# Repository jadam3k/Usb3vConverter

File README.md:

# USB Mini to 3.3V Converter

A simple USB mini to 3.3V converter: easy to build, reliable, and perfect for small electronics projects.

| Interested? [Follow the project!](https://blueprint.hackclub.com/projects/2747?return_to=%2Fusers%2F2170)|
|------------------------------------|

This project focuses on simplicity while providing stable 3.3V output from a USB mini connector.  

## Features

- USB Mini input
- 3.3V regulated output
- Compact PCB design
- Only 3 integrated circuits needed
- Easy to solder and assemble
- Suitable for powering small electronics or logic circuits  

The PCB layout is designed to be simple ;)

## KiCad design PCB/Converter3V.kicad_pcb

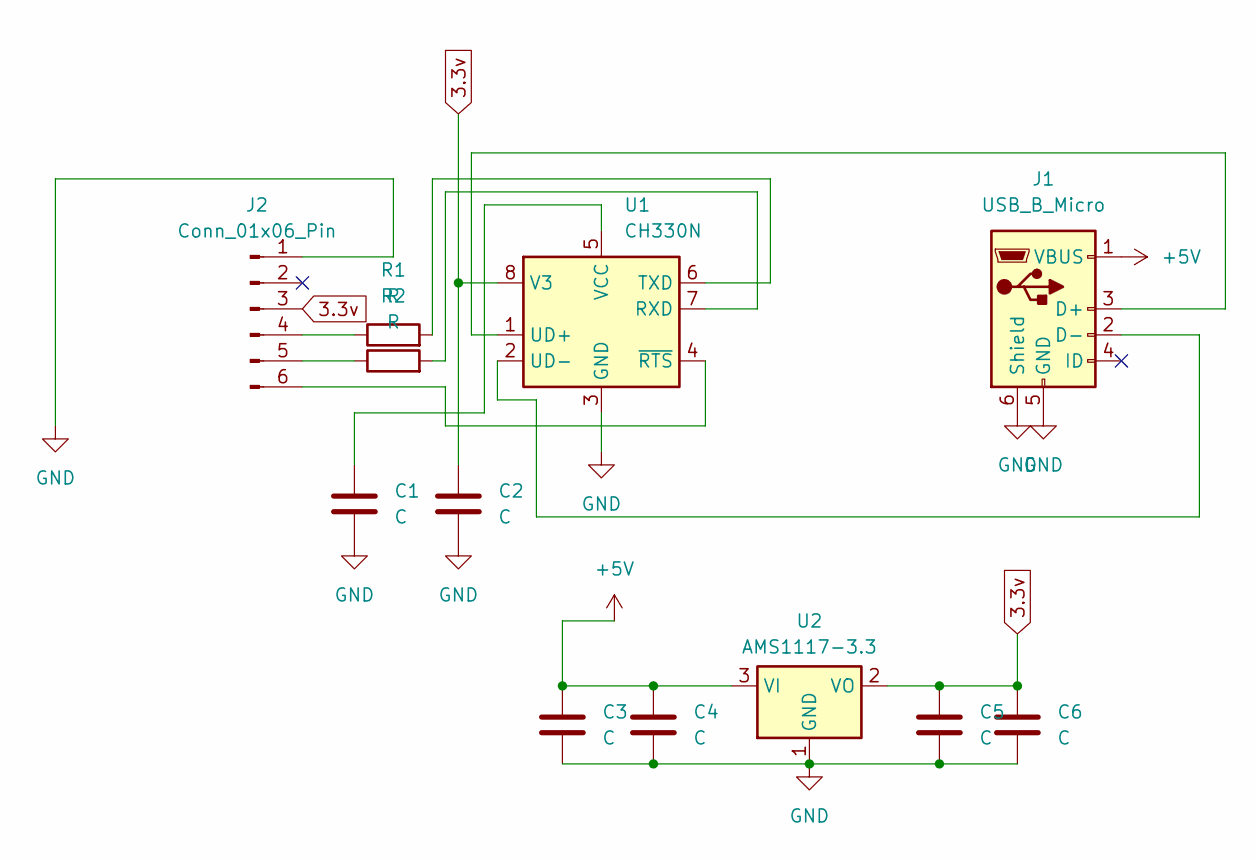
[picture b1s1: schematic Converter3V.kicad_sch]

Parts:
C1, C2: C; CP_Radial_D5.0mm_P2.50mm
C3, C4, C5, C6: C; C_Radial_D6.3mm_H7.0mm_P2.50mm
J1: USB_B_Micro; USB_Micro-B_Amphenol_10103594-0001LF_Horizontal
J2: Conn_01x06_Pin; PinSocket_1x06_P2.54mm_Horizontal
R1, R2: R; R_Axial_DIN0207_L6.3mm_D2.5mm_P7.62mm_Horizontal
U1: CH330N; SOIC-8_3.9x4.9mm_P1.27mm
U2: AMS1117-3.3; SOT-223-3_TabPin2

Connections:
3.3v: C2.1, C5.1, C6.1, J2.3, U1.8 (V3), U2.2 (VO)
+5V: C3.1, C4.1, J1.1 (VBUS), U2.3 (VI)
GND: C1.2, C2.2, C3.2, C4.2, C5.2, C6.2, J1.5 (GND), J1.6 (Shield), J2.1, U1.3 (GND), U2.1 (GND)
unnamed: J1.3 (D+), U1.1 (UD+)
unnamed: J1.2 (D-), U1.2 (UD-)
unnamed: J2.4, R1.1
unnamed: J2.5, R2.1
unnamed: J2.6, U1.4 (~RTS)
unnamed: R2.2, U1.7 (RXD)
unnamed: R1.2, U1.6 (TXD)
unnamed: C1.1, U1.5 (VCC)

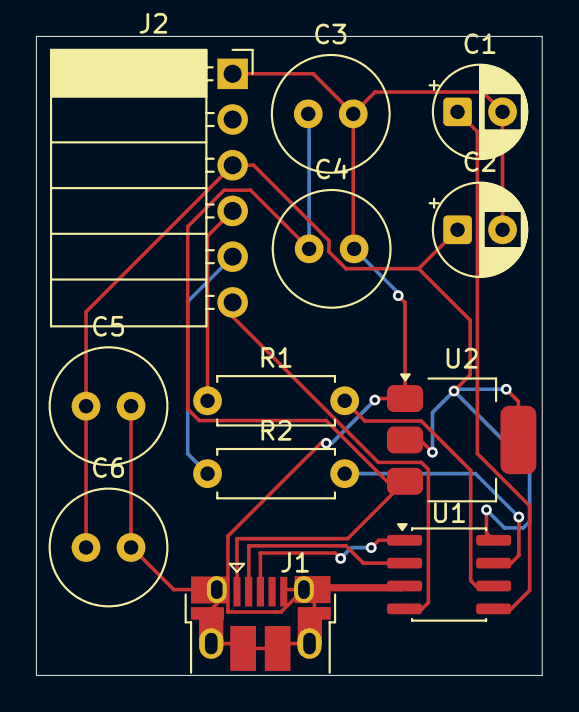
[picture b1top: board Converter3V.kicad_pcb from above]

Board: 2 copper layers, 28.1 x 35.5 mm, 12 parts (0 on the bottom side), 11 nets.

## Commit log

2025-12-14 Revise README for clarity and project details
    Updated README to improve project presentation and removed development journal.
2025-12-14 Update PCB layout description for clarity
